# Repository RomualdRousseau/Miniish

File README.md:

# Miniish - Homebrew 6502 Computer

The goal of this project is to build a 8bit game console based on 6502 CPU.
The entire project is strongly inspired by the work and videos of Ben Eater, but
also Javidx9 and his emulator.

## Mother Board

It is basically the same hardware design presented by Ben Eater. I just cleaned
up the adress control logic to have as mush of the 32K RAM available.

The address plan is:

0000 --------------------------------

//   RAM

8000 --------------------------------

//   LO ROM

D000 --------------------------------

//   IRQ Status

D100 --------------------------------

//   PICTURE PROCESSING UNIT (PORT1B)

D200 --------------------------------

//   AUDIO PROCESSING UNIT (PORT2B)

D300 --------------------------------

//   I/O

D400 --------------------------------

//   Reserved

E000 --------------------------------

//   HI ROM

FFFF --------------------------------

## Picture Processing Unit (PPU)

### VGA Card

The card is built using a FPGA and strongly inspired to the NES PPU and the
capability of PICO-8.

The overall specs of the VGA card is 16 colors with a 128x128 display area using
the VGA 640x480 60Hz standard. The 16 colors are the PICO8 palette.

The VGA card is interfaced to the motherboard through a sprite based unit. The
video ram is not mapped to the computer ram but instead, the CPU sends instructions
to a sprite generator very similar to the NES (greatly based on Javidx9
explanations).

The overall spec of the sprite generator is:

* 1 nametables for the background composed of 16 * 16 tiles. Each tile is 8x8
pixels. Scrolling vertical and horizontal modes are supported.

* 256 sprites with tansparency support. Each sprite is also a tile of 8x8 pixels.

* 64 simultaneous sprites on screen and 16 sprites per scanline

* NMI is generated at each vertical blank

## Audio Procesing Unit (APU)

The card is built using a ATMEGA328p at 20Mhz with the library the_synth of Edgar.

The synthetizer has the overall spec: 

* 4 channels at 20KHz

* 4 waveforms: triangle, square, sinus + noise

* 4 envelopes

* modulation

* IRQ0 is generated as the next data frame callback

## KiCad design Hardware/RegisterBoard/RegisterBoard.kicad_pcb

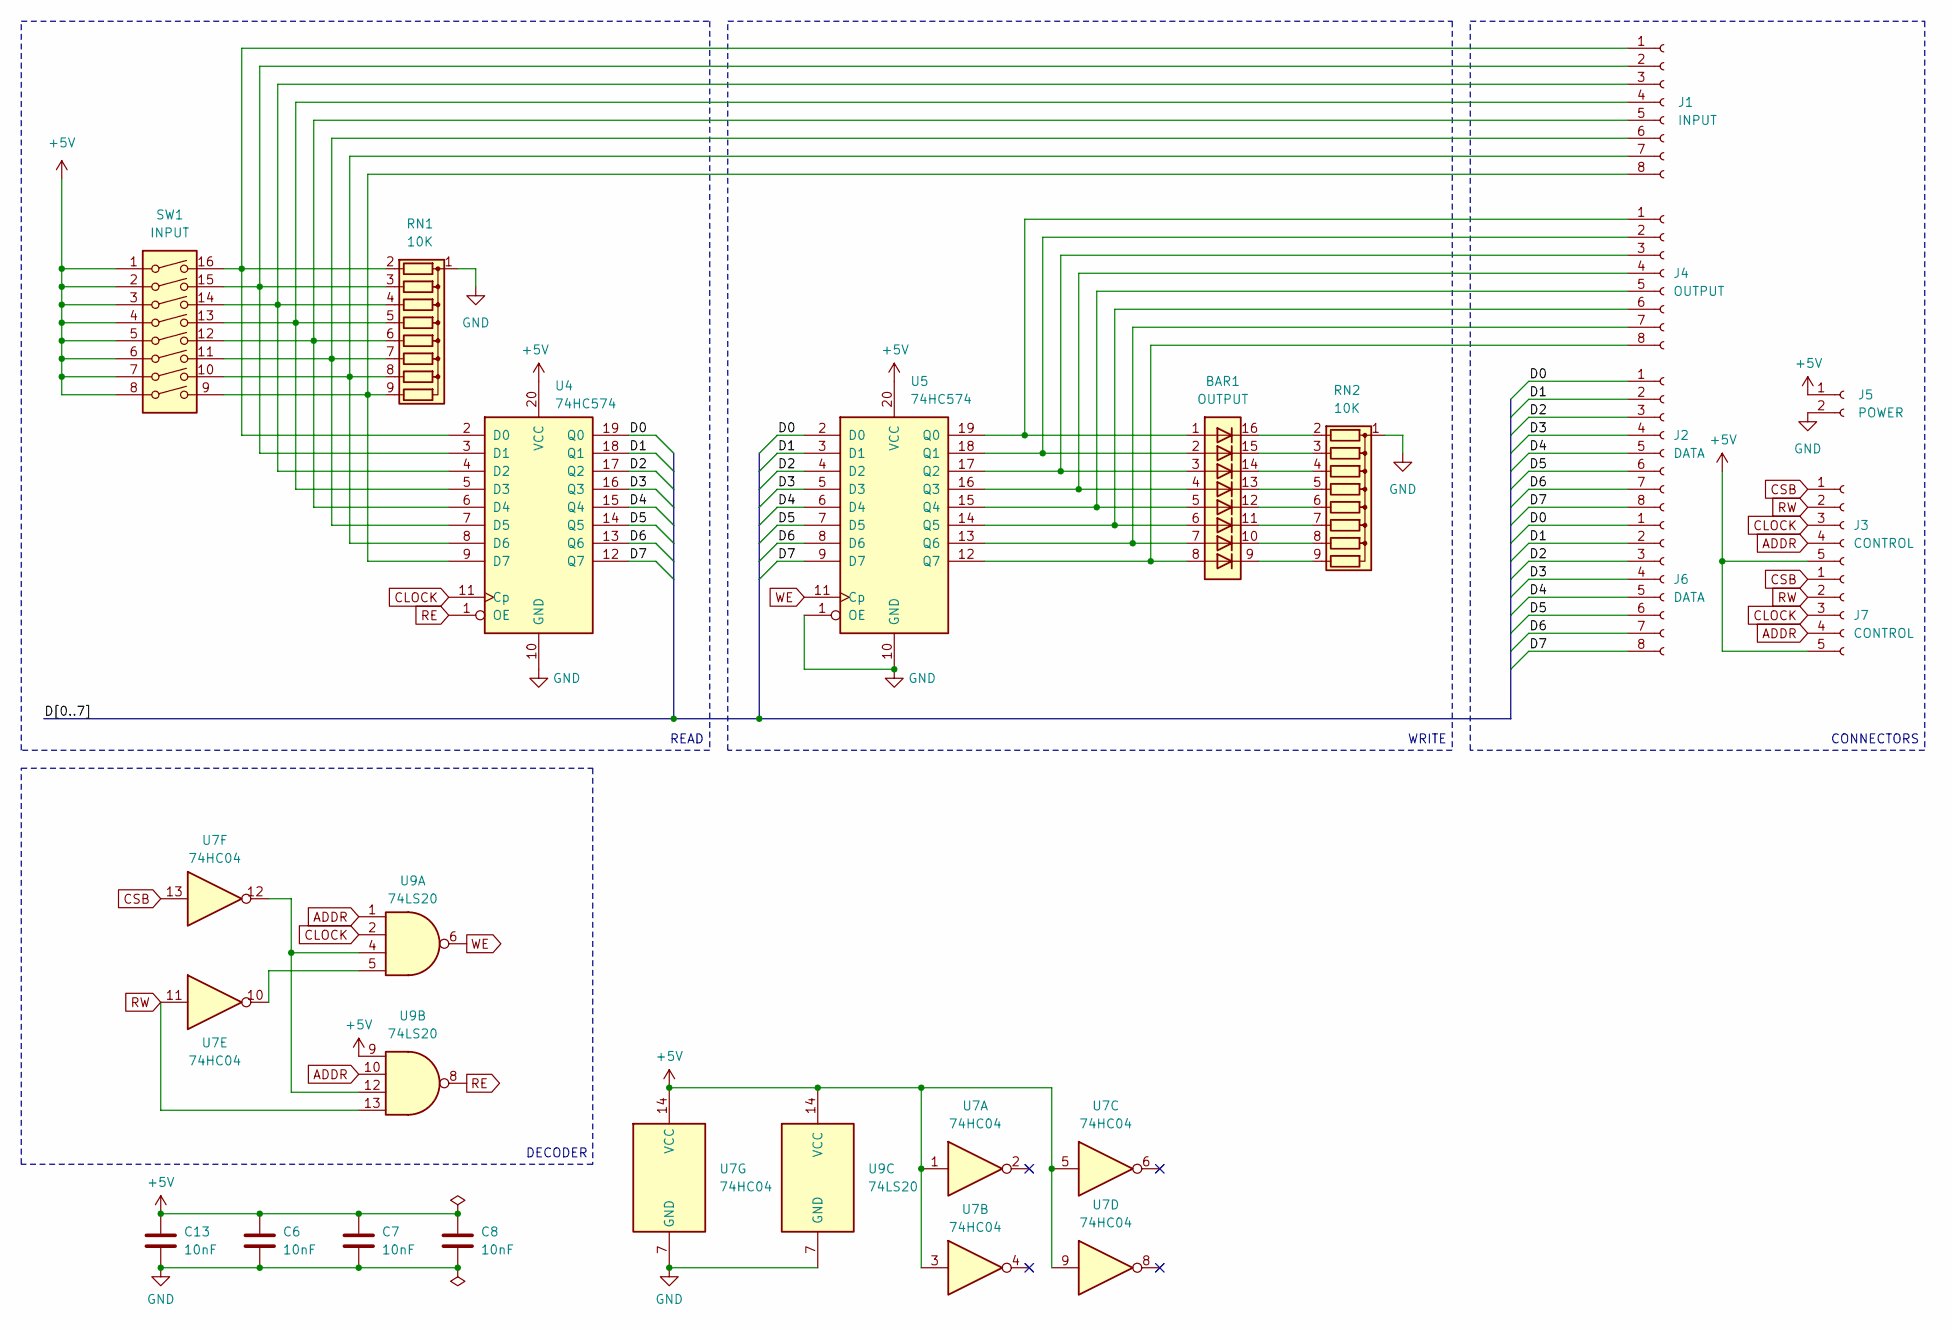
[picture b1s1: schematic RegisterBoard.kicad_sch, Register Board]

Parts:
BAR1: OUTPUT; SSB-LXH100SRW
C6, C7, C8, C13: 10nF; C_Disc_D5.0mm_W2.5mm_P5.00mm
J1: INPUT; PinSocket_1x08_P2.54mm_Vertical
J2, J6: DATA; PinSocket_1x08_P2.54mm_Vertical
J3, J7: CONTROL; PinHeader_1x05_P2.54mm_Vertical
J4: OUTPUT; PinSocket_1x08_P2.54mm_Vertical
J5: POWER; PinSocket_1x02_P2.54mm_Vertical
RN1, RN2: 10K; R_Array_SIP9
SW1: INPUT; SW_DIP_SPSTx08_Slide_9.78x22.5mm_W7.62mm_P2.54mm
U4, U5: 74HC574; DIP-20_W7.62mm
U7: 74HC04; DIP-14_W7.62mm
U9: 74LS20; DIP-14_W7.62mm

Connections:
+5V: C6.1, C7.1, C8.1, C13.1, J3.5, J5.1, J7.5, SW1.1, SW1.2, SW1.3, SW1.4, SW1.5, SW1.6, SW1.7, SW1.8, U4.20 (VCC), U5.20 (VCC), U7.1, U7.3, U7.5, U7.9, U7.14 (VCC), U9.9, U9.14 (VCC)
/D0: J2.1, J6.1, U4.19 (Q0), U5.2 (D0)
/D1: J2.2, J6.2, U4.18 (Q1), U5.3 (D1)
/D2: J2.3, J6.3, U4.17 (Q2), U5.4 (D2)
/D3: J2.4, J6.4, U4.16 (Q3), U5.5 (D3)
/D4: J2.5, J6.5, U4.15 (Q4), U5.6 (D4)
/D5: J2.6, J6.6, U4.14 (Q5), U5.7 (D5)
/D6: J2.7, J6.7, U4.13 (Q6), U5.8 (D6)
/D7: J2.8, J6.8, U4.12 (Q7), U5.9 (D7)
ADDR: J3.4, J7.4, U9.1, U9.10
CLOCK: J3.3, J7.3, U4.11 (Cp), U9.2
CSB: J3.1, J7.1, U7.13
GND: C6.2, C7.2, C8.2, C13.2, J5.2, RN1.1 (common), RN2.1 (common), U4.10 (GND), U5.1 (OE), U5.10 (GND), U7.7 (GND), U9.7 (GND)
unnamed: J1.1, RN1.2 (R1), SW1.16, U4.2 (D0)
unnamed: J1.2, RN1.3 (R2), SW1.15, U4.3 (D1)
unnamed: J1.3, RN1.4 (R3), SW1.14, U4.4 (D2)
unnamed: J1.4, RN1.5 (R4), SW1.13, U4.5 (D3)
unnamed: J1.5, RN1.6 (R5), SW1.12, U4.6 (D4)
unnamed: J1.6, RN1.7 (R6), SW1.11, U4.7 (D5)
unnamed: J1.7, RN1.8 (R7), SW1.10, U4.8 (D6)
unnamed: J1.8, RN1.9 (R8), SW1.9, U4.9 (D7)
unnamed: BAR1.1 (A), J4.1, U5.19 (Q0)
unnamed: BAR1.2 (A), J4.2, U5.18 (Q1)
unnamed: BAR1.3 (A), J4.3, U5.17 (Q2)
unnamed: BAR1.4 (A), J4.4, U5.16 (Q3)
unnamed: BAR1.5 (A), J4.5, U5.15 (Q4)
unnamed: BAR1.6 (A), J4.6, U5.14 (Q5)
unnamed: BAR1.7 (A), J4.7, U5.13 (Q6)
unnamed: BAR1.8 (A), J4.8, U5.12 (Q7)
unnamed: BAR1.16 (K), RN2.2 (R1)
unnamed: BAR1.15 (K), RN2.3 (R2)
unnamed: BAR1.14 (K), RN2.4 (R3)
unnamed: BAR1.13 (K), RN2.5 (R4)
unnamed: BAR1.12 (K), RN2.6 (R5)
unnamed: BAR1.11 (K), RN2.7 (R6)
unnamed: BAR1.10 (K), RN2.8 (R7)
unnamed: BAR1.9 (K), RN2.9 (R8)
unnamed: U7.10, U9.5
unnamed: U7.12, U9.4, U9.12
RE: U4.1 (OE), U9.8
RW: J3.2, J7.2, U7.11, U9.13
WE: U5.11 (Cp), U9.6

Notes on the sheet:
WRITE
CONNECTORS
DECODER
READ

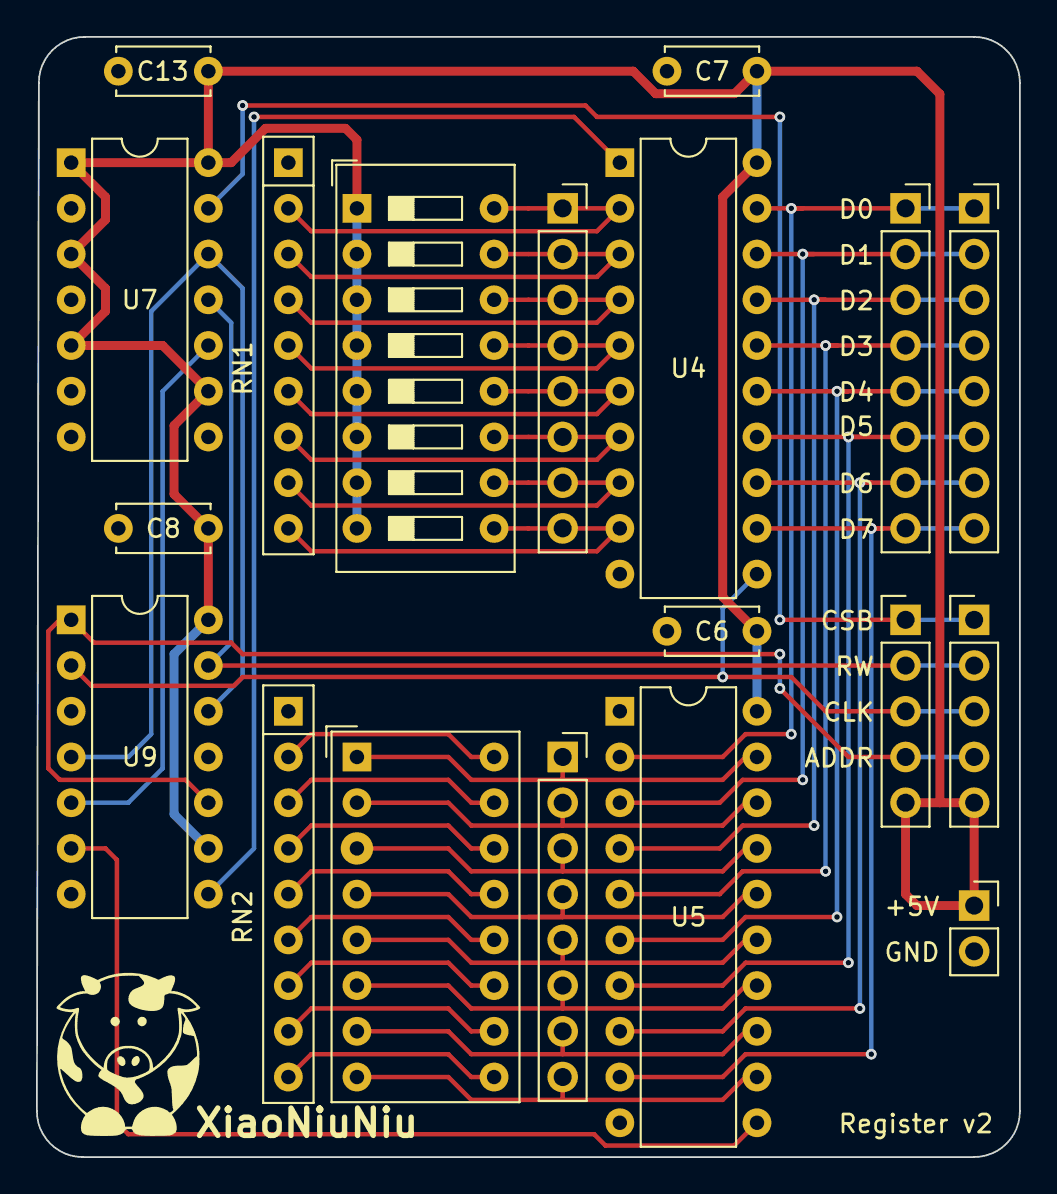
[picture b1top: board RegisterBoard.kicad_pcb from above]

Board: 2 copper layers, 54.6 x 62.2 mm, 20 parts (0 on the bottom side), 42 nets.

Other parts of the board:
XiaoNiuNiu: LOGO; VerySmallCow

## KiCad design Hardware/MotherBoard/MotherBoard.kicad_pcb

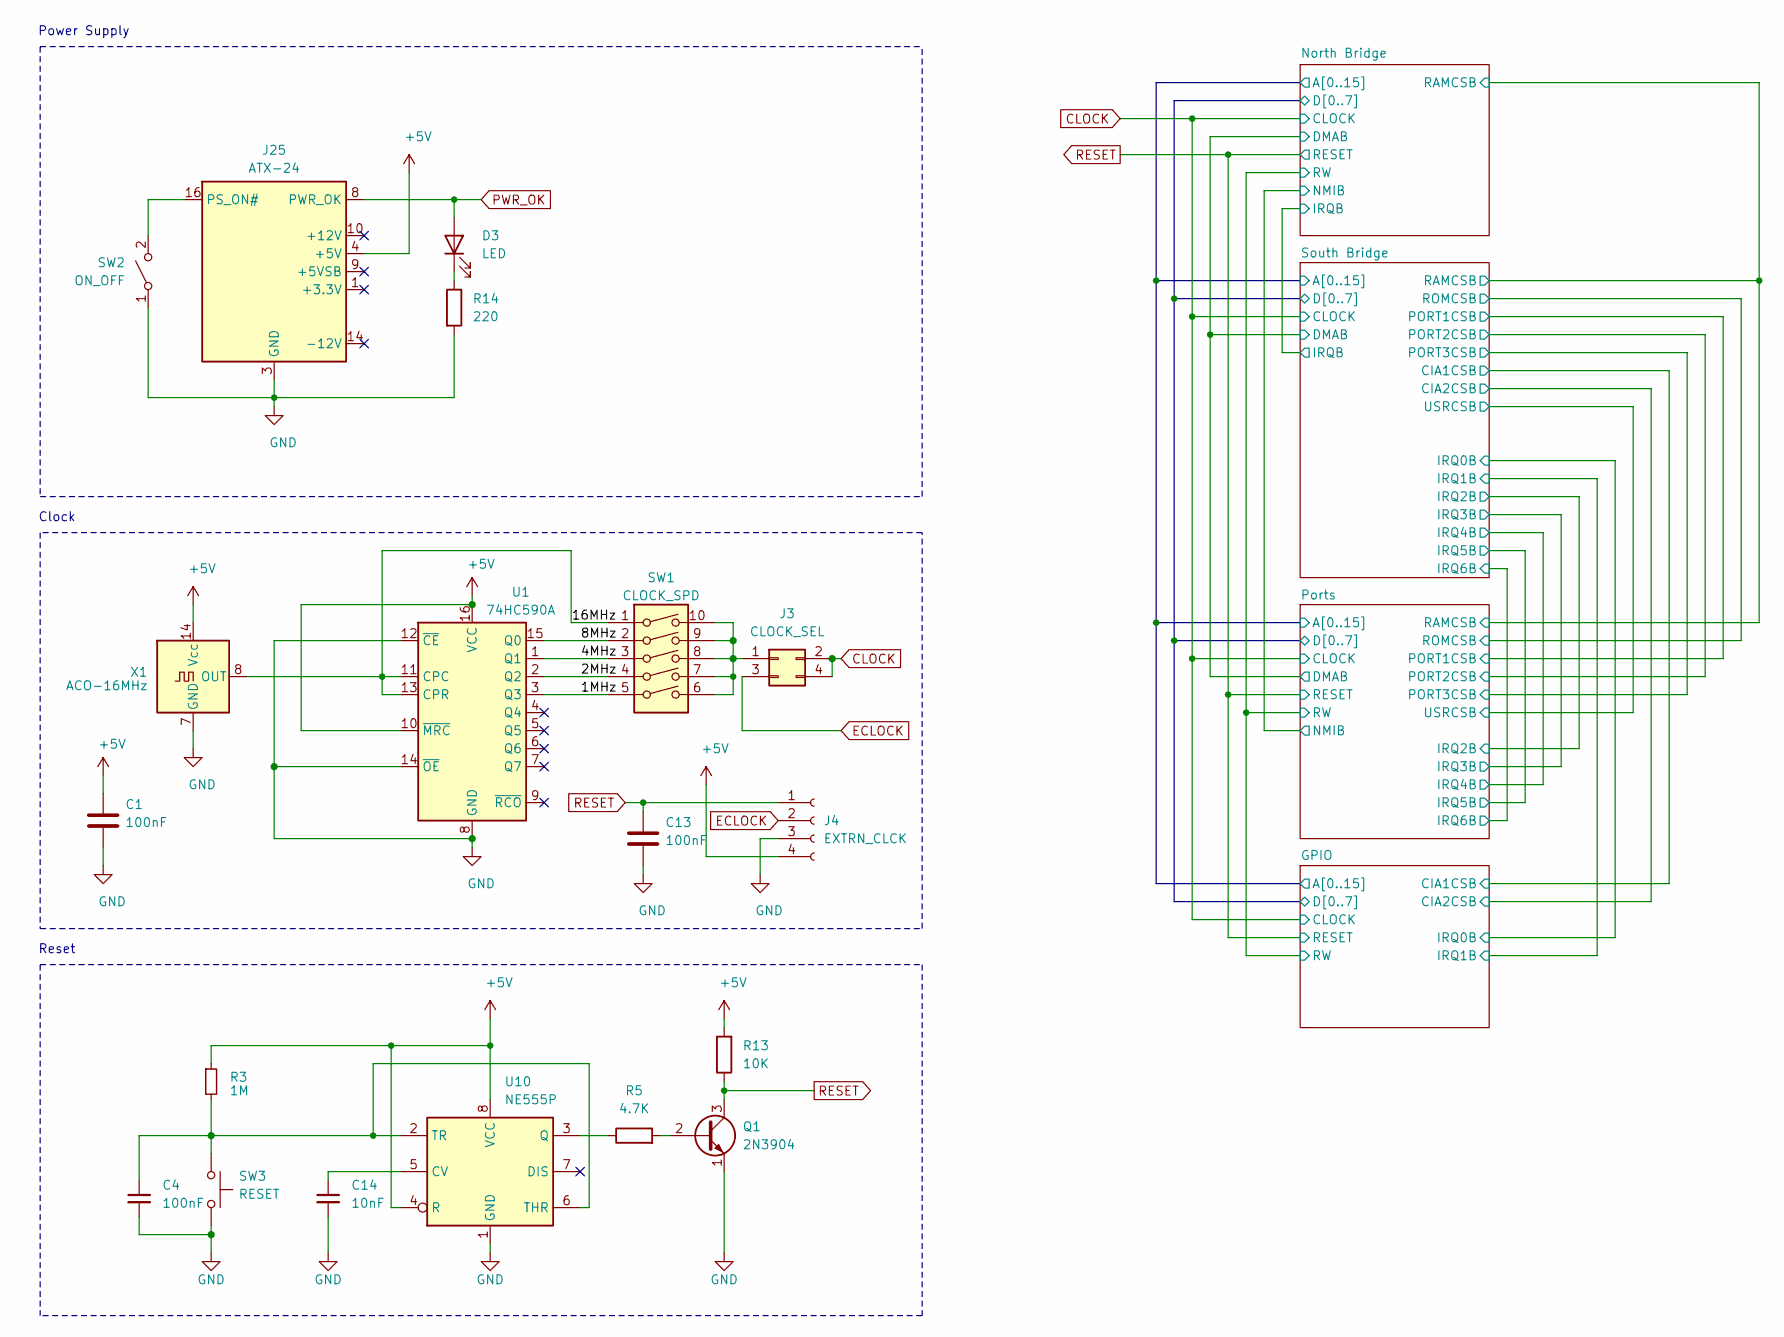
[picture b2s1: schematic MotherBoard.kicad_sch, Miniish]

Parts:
C1, C4, C13: 100nF; C_Disc_D5.0mm_W2.5mm_P2.50mm
C14: 10nF; C_Disc_D5.0mm_W2.5mm_P2.50mm
D3: LED; LED_D5.0mm
J3: CLOCK_SEL; PinHeader_2x02_P2.54mm_Vertical
J4: EXTRN_CLCK; PinHeader_1x04_P2.54mm_Vertical
J25: ATX-24; Molex_Mini-Fit_Jr_5566-24A_2x12_P4.20mm_Vertical
Q1: 2N3904; TO-92_Inline
R3: 1M; R_Axial_DIN0207_L6.3mm_D2.5mm_P10.16mm_Horizontal
R5: 4.7K; R_Axial_DIN0207_L6.3mm_D2.5mm_P10.16mm_Horizontal
R13: 10K; R_Axial_DIN0207_L6.3mm_D2.5mm_P10.16mm_Horizontal
R14: 220; R_Axial_DIN0207_L6.3mm_D2.5mm_P10.16mm_Horizontal
SW1: CLOCK_SPD; SW_DIP_SPSTx05_Slide_6.7x14.26mm_W7.62mm_P2.54mm_LowProfile
SW2: ON_OFF; SW_E-Switch_EG1224_SPDT_Angled
SW3: RESET; SW_Tactile_SPST_Angled_PTS645Vx83-2LFS
U1: 74HC590A; DIP-16_W7.62mm
U10: NE555P; DIP-8_W7.62mm
X1: ACO-16MHz; Oscillator_DIP-14

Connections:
+5V: C1.1, J4.4, J25.4 (+5V), J25.6 (+5V), J25.21 (+5V), J25.22 (+5V), J25.23 (+5V), R3.1, R13.2, U1.10 (~MRC), U1.16 (VCC), U10.4 (R), U10.8 (VCC), X1.14 (Vcc); also elsewhere on the board
/1MHz: SW1.5, U1.3 (Q3)
/2MHz: SW1.4, U1.2 (Q2)
/4MHz: SW1.3, U1.1 (Q1)
/8MHz: SW1.2, U1.15 (Q0)
/16MHz: SW1.1, U1.11 (CPC), U1.13 (CPR), X1.8 (OUT)
CLOCK: J3.2, J3.4; also elsewhere on the board
ECLOCK: J3.3, J4.2
GND: C1.2, C4.2, C13.2, C14.2, J4.3, J25.3 (GND), J25.5 (GND), J25.7 (GND), J25.15 (GND), J25.17 (GND), J25.18 (GND), J25.19 (GND), J25.24 (GND), Q1.1 (E), R14.2, SW2.1 (A), SW3.2, U1.8 (GND), U1.12 (~CE), U1.14 (~OE), U10.1 (GND), X1.7 (GND); also elsewhere on the board
unnamed: D3.1 (K), R14.1
unnamed: J3.1, SW1.6, SW1.7, SW1.8, SW1.9, SW1.10
unnamed: J25.16 (PS_ON#), SW2.2 (B)
unnamed: Q1.2 (B), R5.2
unnamed: C14.1, U10.5 (CV)
unnamed: R5.1, U10.3 (Q)
unnamed: C4.1, R3.2, SW3.1, U10.2 (TR), U10.6 (THR)
PWR_OK: D3.2 (A), J25.8 (PWR_OK)
RESET: C13.1, J4.1, Q1.3 (C), R13.1; also elsewhere on the board

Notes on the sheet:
Reset
Power Supply
Clock

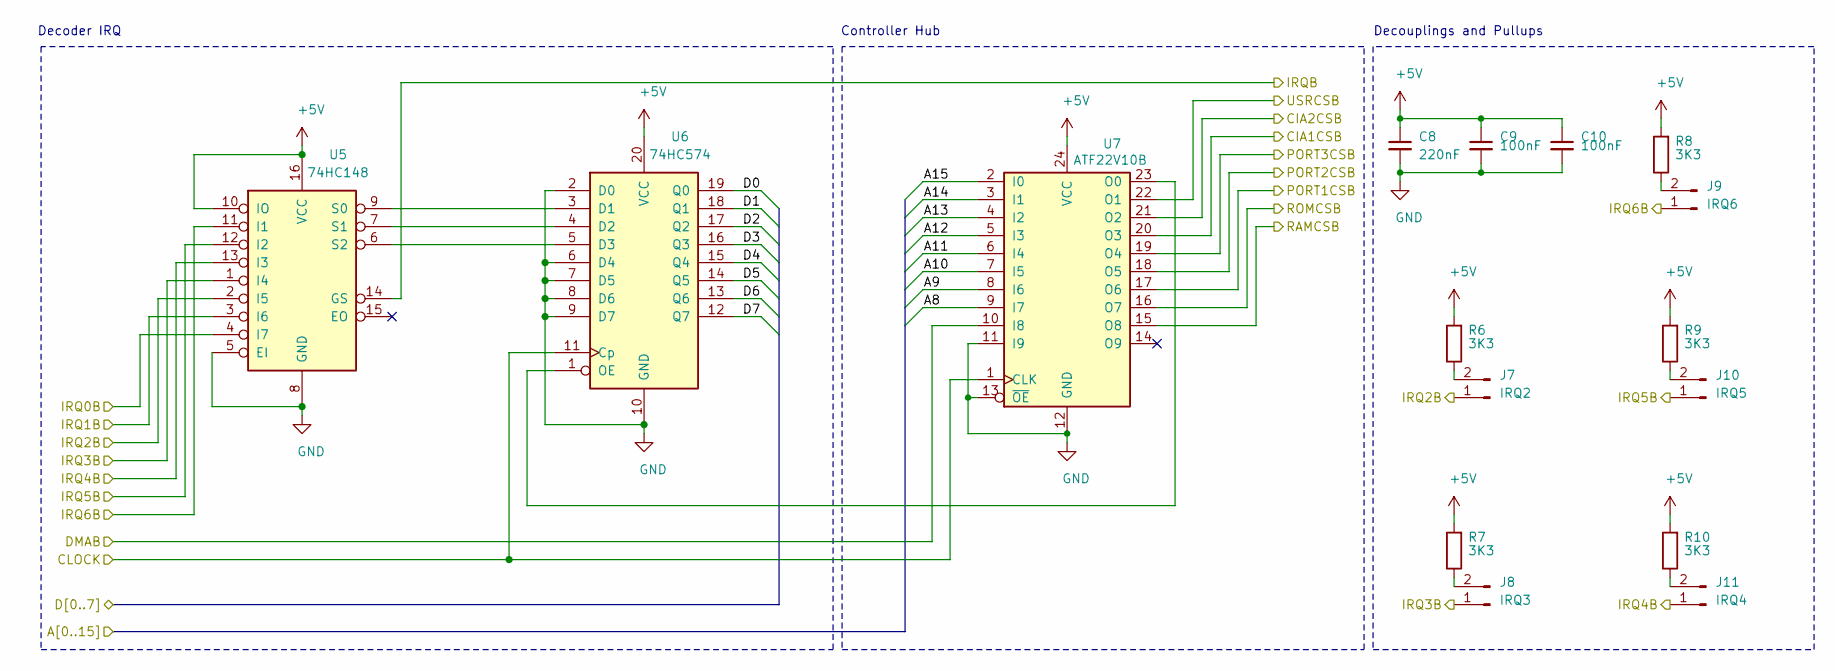
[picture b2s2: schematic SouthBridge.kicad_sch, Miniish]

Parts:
C8: 220nF; C_Disc_D5.0mm_W2.5mm_P2.50mm
C9, C10: 100nF; C_Disc_D5.0mm_W2.5mm_P2.50mm
J7: IRQ2; PinHeader_1x02_P2.54mm_Vertical
J8: IRQ3; PinHeader_1x02_P2.54mm_Vertical
J9: IRQ6; PinHeader_1x02_P2.54mm_Vertical
J10: IRQ5; PinHeader_1x02_P2.54mm_Vertical
J11: IRQ4; PinHeader_1x02_P2.54mm_Vertical
R6, R7, R8, R9, R10: 3K3; R_Axial_DIN0207_L6.3mm_D2.5mm_P10.16mm_Horizontal
U5: 74HC148; DIP-16_W7.62mm
U6: 74HC574; DIP-20_W7.62mm
U7: ATF22V10B; DIP-24_W7.62mm

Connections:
+5V: C8.1, C9.1, C10.1, R6.2, R7.2, R8.2, R9.2, R10.2, U5.10 (IO), U5.16 (VCC), U6.20 (VCC), U7.24 (VCC); also elsewhere on the board
/GPIO/A8: U7.9 (I7); also elsewhere on the board
/GPIO/A9: U7.8 (I6); also elsewhere on the board
/GPIO/A10: U7.7 (I5); also elsewhere on the board
/GPIO/A11: U7.6 (I4); also elsewhere on the board
/GPIO/A12: U7.5 (I3); also elsewhere on the board
/GPIO/A13: U7.4 (I2); also elsewhere on the board
/GPIO/A14: U7.3 (I1); also elsewhere on the board
/GPIO/A15: U7.2 (I0); also elsewhere on the board
/GPIO/CIA1CSB: U7.20 (O3); also elsewhere on the board
/GPIO/CIA2CSB: U7.21 (O2); also elsewhere on the board
/GPIO/D0: U6.19 (Q0); also elsewhere on the board
/GPIO/D1: U6.18 (Q1); also elsewhere on the board
/GPIO/D2: U6.17 (Q2); also elsewhere on the board
/GPIO/D3: U6.16 (Q3); also elsewhere on the board
/GPIO/D4: U6.15 (Q4); also elsewhere on the board
/GPIO/D5: U6.14 (Q5); also elsewhere on the board
/GPIO/D6: U6.13 (Q6); also elsewhere on the board
/GPIO/D7: U6.12 (Q7); also elsewhere on the board
/GPIO/IRQ0B: U5.4 (I7); also elsewhere on the board
/GPIO/IRQ1B: U5.3 (I6); also elsewhere on the board
/North Bridge/DMAB: U7.10 (I8); also elsewhere on the board
/North Bridge/IRQB: U5.14 (GS); also elsewhere on the board
/North Bridge/RAMCSB: U7.15 (O8); also elsewhere on the board
/Ports/IRQ2B: J7.1, U5.2 (I5)
/Ports/IRQ3B: J8.1, U5.1 (I4); also elsewhere on the board
/Ports/IRQ4B: J11.1, U5.13 (I3); also elsewhere on the board
/Ports/IRQ5B: J10.1, U5.12 (I2); also elsewhere on the board
/Ports/IRQ6B: J9.1, U5.11 (I1); also elsewhere on the board
/Ports/PORT1CSB: U7.17 (O6); also elsewhere on the board
/Ports/PORT2CSB: U7.18 (O5); also elsewhere on the board
/Ports/PORT3CSB: U7.19 (O4); also elsewhere on the board
/Ports/ROMCSB: U7.16 (O7); also elsewhere on the board
/Ports/USRCSB: U7.22 (O1)
CLOCK: U6.11 (Cp), U7.1 (CLK); also elsewhere on the board
GND: C8.2, C9.2, C10.2, U5.5 (EI), U5.8 (GND), U6.2 (D0), U6.6 (D4), U6.7 (D5), U6.8 (D6), U6.9 (D7), U6.10 (GND), U7.11 (I9), U7.12 (GND), U7.13 (~OE); also elsewhere on the board
unnamed: J7.2, R6.1
unnamed: J8.2, R7.1
unnamed: J9.2, R8.1
unnamed: J10.2, R9.1
unnamed: J11.2, R10.1
unnamed: U5.9 (S0), U6.3 (D1)
unnamed: U5.7 (S1), U6.4 (D2)
unnamed: U5.6 (S2), U6.5 (D3)
unnamed: U6.1 (OE), U7.23 (O0)

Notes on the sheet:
Decouplings and Pullups
Decoder IRQ
Controller Hub

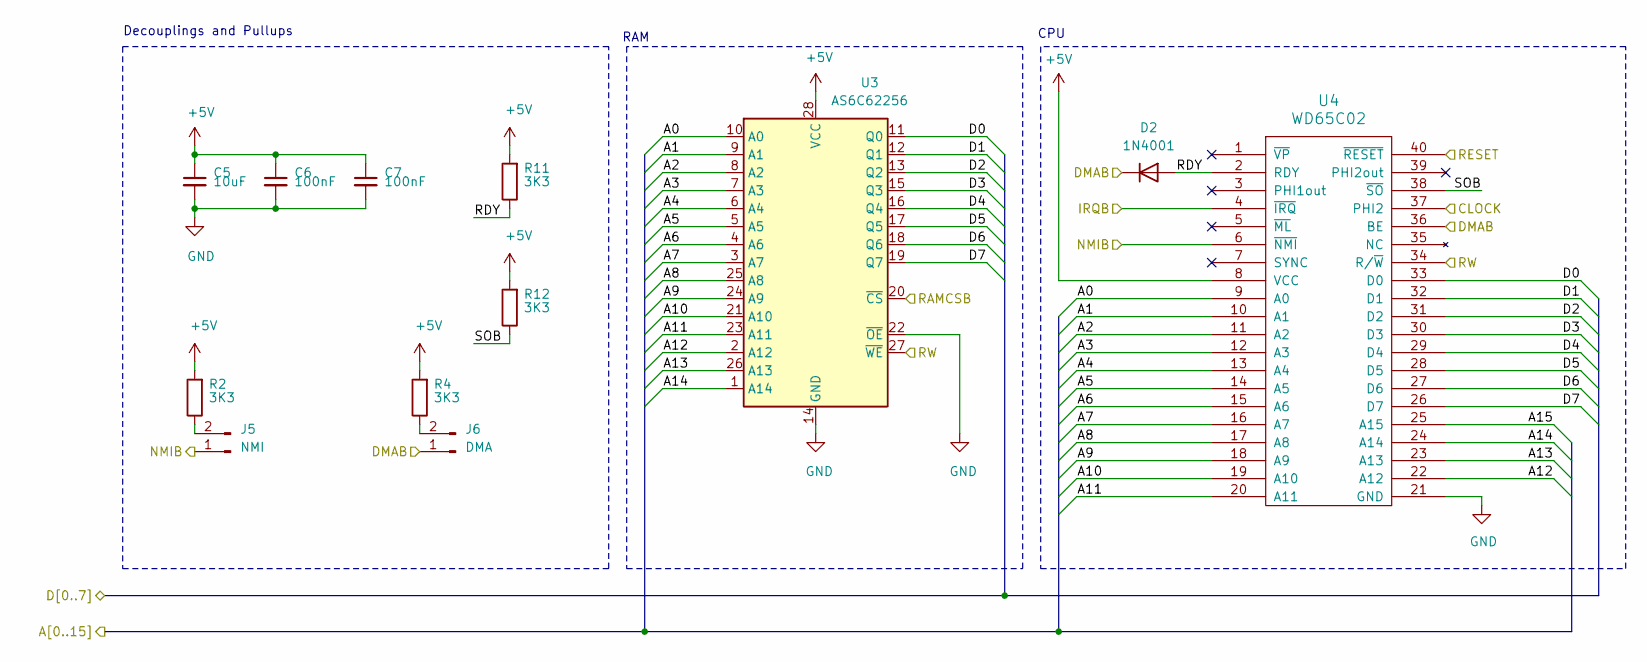
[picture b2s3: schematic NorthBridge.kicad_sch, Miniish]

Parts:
C5: 10uF; C_Radial_D5.0mm_H11.0mm_P2.00mm
C6, C7: 100nF; C_Disc_D5.0mm_W2.5mm_P2.50mm
D2: 1N4001; D_DO-41_SOD81_P10.16mm_Horizontal
J5: NMI; PinHeader_1x02_P2.54mm_Vertical
J6: DMA; PinHeader_1x02_P2.54mm_Vertical
R2, R4, R11, R12: 3K3; R_Axial_DIN0207_L6.3mm_D2.5mm_P10.16mm_Horizontal
U3: AS6C62256; DIP-28_W15.24mm
U4: WD65C02; DIP-40_W15.24mm

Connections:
+5V: C5.1, C6.1, C7.1, R2.2, R4.2, R11.2, R12.2, U3.28 (VCC), U4.8 (VCC); also elsewhere on the board
/GPIO/A0: U3.10 (A0), U4.9 (A0); also elsewhere on the board
/GPIO/A1: U3.9 (A1), U4.10 (A1); also elsewhere on the board
/GPIO/A2: U3.8 (A2), U4.11 (A2); also elsewhere on the board
/GPIO/A3: U3.7 (A3), U4.12 (A3); also elsewhere on the board
/GPIO/A4: U3.6 (A4), U4.13 (A4); also elsewhere on the board
/GPIO/A5: U3.5 (A5), U4.14 (A5); also elsewhere on the board
/GPIO/A6: U3.4 (A6), U4.15 (A6); also elsewhere on the board
/GPIO/A7: U3.3 (A7), U4.16 (A7); also elsewhere on the board
/GPIO/A8: U3.25 (A8), U4.17 (A8); also elsewhere on the board
/GPIO/A9: U3.24 (A9), U4.18 (A9); also elsewhere on the board
/GPIO/A10: U3.21 (A10), U4.19 (A10); also elsewhere on the board
/GPIO/A11: U3.23 (A11), U4.20 (A11); also elsewhere on the board
/GPIO/A12: U3.2 (A12), U4.22 (A12); also elsewhere on the board
/GPIO/A13: U3.26 (A13), U4.23 (A13); also elsewhere on the board
/GPIO/A14: U3.1 (A14), U4.24 (A14); also elsewhere on the board
/GPIO/A15: U4.25 (A15); also elsewhere on the board
/GPIO/D0: U3.11 (Q0), U4.33 (D0); also elsewhere on the board
/GPIO/D1: U3.12 (Q1), U4.32 (D1); also elsewhere on the board
/GPIO/D2: U3.13 (Q2), U4.31 (D2); also elsewhere on the board
/GPIO/D3: U3.15 (Q3), U4.30 (D3); also elsewhere on the board
/GPIO/D4: U3.16 (Q4), U4.29 (D4); also elsewhere on the board
/GPIO/D5: U3.17 (Q5), U4.28 (D5); also elsewhere on the board
/GPIO/D6: U3.18 (Q6), U4.27 (D6); also elsewhere on the board
/GPIO/D7: U3.19 (Q7), U4.26 (D7); also elsewhere on the board
/GPIO/RW: U3.27 (~WE), U4.34 (R/~W); also elsewhere on the board
/North Bridge/DMAB: D2.1 (K), J6.1, U4.36 (BE); also elsewhere on the board
/North Bridge/IRQB: U4.4 (~IRQ); also elsewhere on the board
/North Bridge/NMIB: J5.1, U4.6 (~NMI); also elsewhere on the board
/North Bridge/RAMCSB: U3.20 (~CS); also elsewhere on the board
/North Bridge/RDY: D2.2 (A), R11.1, U4.2 (RDY)
/North Bridge/SOB: R12.1, U4.38 (~SO)
CLOCK: U4.37 (PHI2); also elsewhere on the board
GND: C5.2, C6.2, C7.2, U3.14 (GND), U3.22 (~OE), U4.21 (GND); also elsewhere on the board
unnamed: J5.2, R2.1
unnamed: J6.2, R4.1
RESET: U4.40 (~RESET); also elsewhere on the board

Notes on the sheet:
CPU
RAM
Decouplings and Pullups

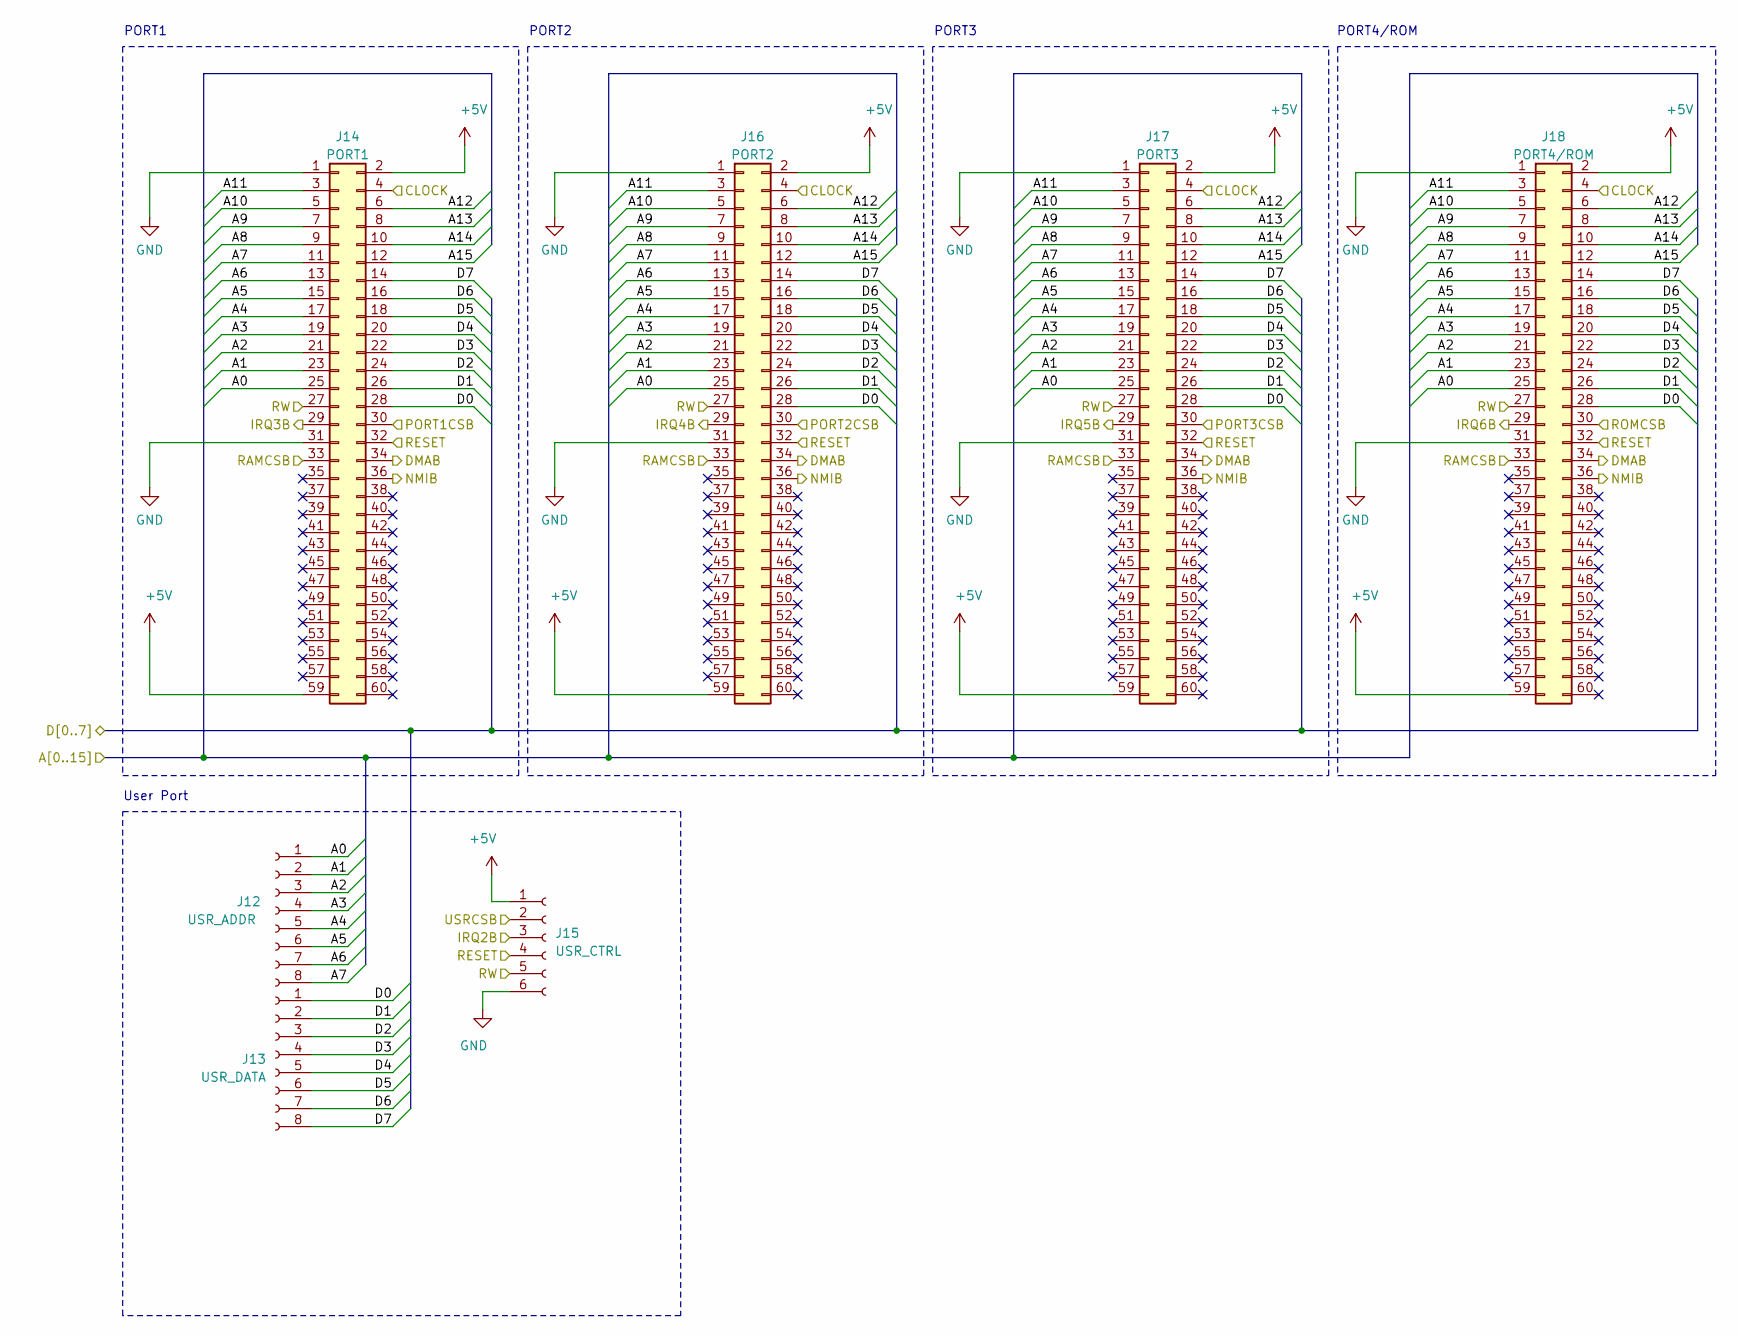
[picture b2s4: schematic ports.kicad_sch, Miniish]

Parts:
J12: USR_ADDR; PinHeader_1x08_P2.54mm_Vertical
J13: USR_DATA; PinHeader_1x08_P2.54mm_Vertical
J14: PORT1; NES_Cartdrige
J15: USR_CTRL; PinHeader_2x03_P2.54mm_Vertical
J16: PORT2; NES_Cartdrige
J17: PORT3; NES_Cartdrige
J18: PORT4/ROM; NES_Cartdrige

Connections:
+5V: J14.2, J14.59, J15.1, J16.2, J16.59, J17.2, J17.59, J18.2, J18.59; also elsewhere on the board
/GPIO/A0: J12.1, J14.25, J16.25, J17.25, J18.25; also elsewhere on the board
/GPIO/A1: J12.2, J14.23, J16.23, J17.23, J18.23; also elsewhere on the board
/GPIO/A2: J12.3, J14.21, J16.21, J17.21, J18.21; also elsewhere on the board
/GPIO/A3: J12.4, J14.19, J16.19, J17.19, J18.19; also elsewhere on the board
/GPIO/A4: J12.5, J14.17, J16.17, J17.17, J18.17; also elsewhere on the board
/GPIO/A5: J12.6, J14.15, J16.15, J17.15, J18.15; also elsewhere on the board
/GPIO/A6: J12.7, J14.13, J16.13, J17.13, J18.13; also elsewhere on the board
/GPIO/A7: J12.8, J14.11, J16.11, J17.11, J18.11; also elsewhere on the board
/GPIO/A8: J14.9, J16.9, J17.9, J18.9; also elsewhere on the board
/GPIO/A9: J14.7, J16.7, J17.7, J18.7; also elsewhere on the board
/GPIO/A10: J14.5, J16.5, J17.5, J18.5; also elsewhere on the board
/GPIO/A11: J14.3, J16.3, J17.3, J18.3; also elsewhere on the board
/GPIO/A12: J14.6, J16.6, J17.6, J18.6; also elsewhere on the board
/GPIO/A13: J14.8, J16.8, J17.8, J18.8; also elsewhere on the board
/GPIO/A14: J14.10, J16.10, J17.10, J18.10; also elsewhere on the board
/GPIO/A15: J14.12, J16.12, J17.12, J18.12; also elsewhere on the board
/GPIO/D0: J13.1, J14.28, J16.28, J17.28, J18.28; also elsewhere on the board
/GPIO/D1: J13.2, J14.26, J16.26, J17.26, J18.26; also elsewhere on the board
/GPIO/D2: J13.3, J14.24, J16.24, J17.24, J18.24; also elsewhere on the board
/GPIO/D3: J13.4, J14.22, J16.22, J17.22, J18.22; also elsewhere on the board
/GPIO/D4: J13.5, J14.20, J16.20, J17.20, J18.20; also elsewhere on the board
/GPIO/D5: J13.6, J14.18, J16.18, J17.18, J18.18; also elsewhere on the board
/GPIO/D6: J13.7, J14.16, J16.16, J17.16, J18.16; also elsewhere on the board
/GPIO/D7: J13.8, J14.14, J16.14, J17.14, J18.14; also elsewhere on the board
/GPIO/RW: J14.27, J15.5, J16.27, J17.27, J18.27; also elsewhere on the board
/North Bridge/DMAB: J14.34, J16.34, J17.34, J18.34; also elsewhere on the board
/North Bridge/NMIB: J14.36, J16.36, J17.36, J18.36; also elsewhere on the board
/North Bridge/RAMCSB: J14.33, J16.33, J17.33, J18.33; also elsewhere on the board
/Ports/IRQ3B: J14.29; also elsewhere on the board
/Ports/IRQ4B: J16.29; also elsewhere on the board
/Ports/IRQ5B: J17.29; also elsewhere on the board
/Ports/IRQ6B: J18.29; also elsewhere on the board
/Ports/PORT1CSB: J14.30; also elsewhere on the board
/Ports/PORT2CSB: J16.30; also elsewhere on the board
/Ports/PORT3CSB: J17.30; also elsewhere on the board
/Ports/ROMCSB: J18.30; also elsewhere on the board
CLOCK: J14.4, J16.4, J17.4, J18.4; also elsewhere on the board
GND: J14.1, J14.31, J15.6, J16.1, J16.31, J17.1, J17.31, J18.1, J18.31; also elsewhere on the board
RESET: J14.32, J15.4, J16.32, J17.32, J18.32; also elsewhere on the board

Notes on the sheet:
PORT1
PORT3
PORT4/ROM
User Port
PORT2

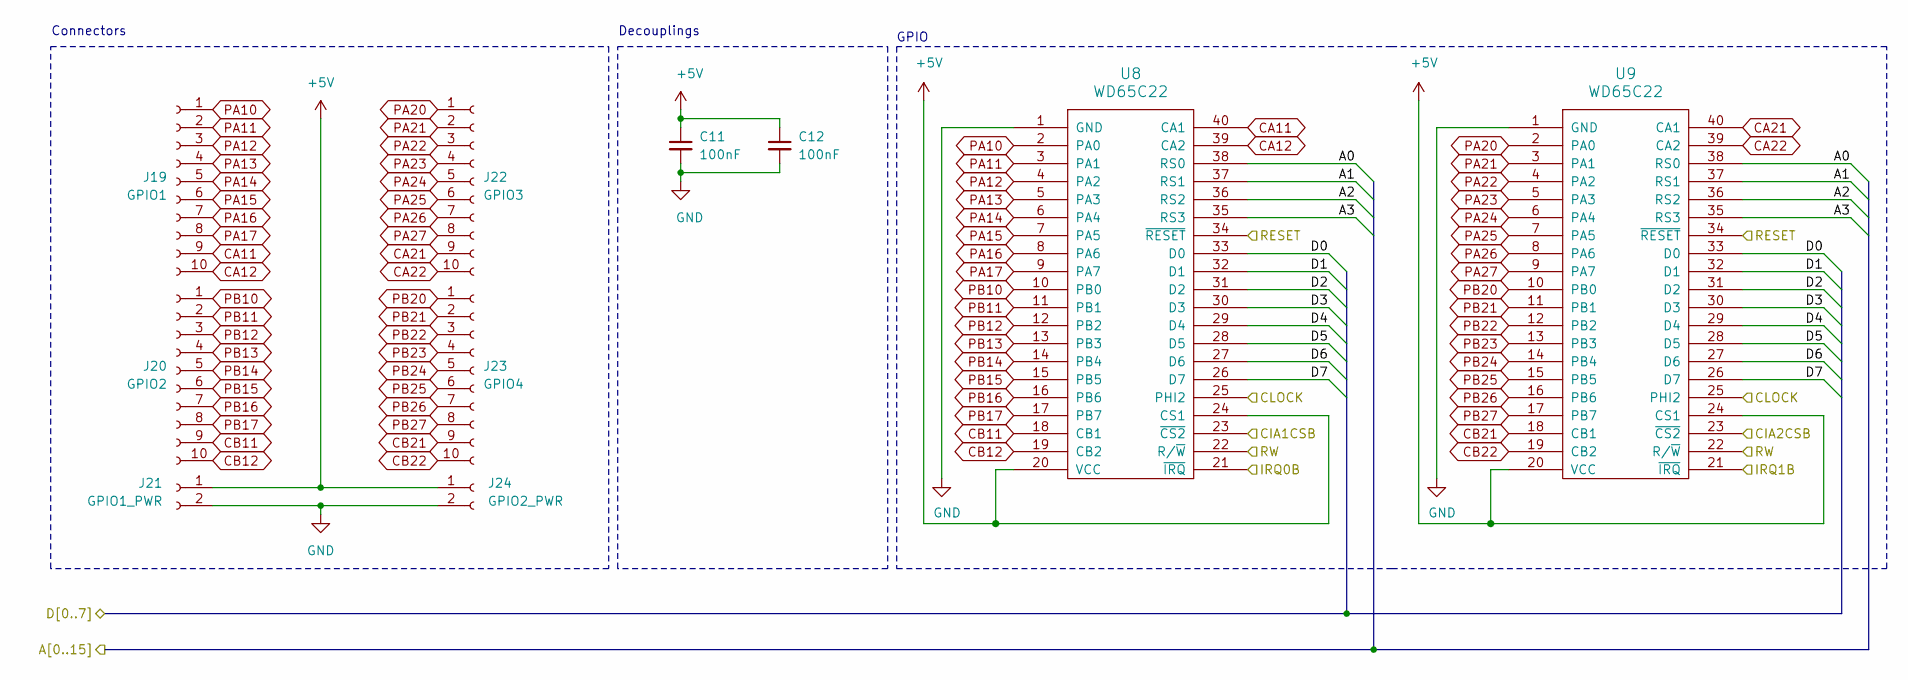
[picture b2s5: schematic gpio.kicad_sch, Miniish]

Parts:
C11, C12: 100nF; C_Disc_D5.0mm_W2.5mm_P2.50mm
J19: GPIO1; PinSocket_1x10_P2.54mm_Vertical
J20: GPIO2; PinSocket_1x10_P2.54mm_Vertical
J21: GPIO1_PWR; PinSocket_1x02_P2.54mm_Vertical
J22: GPIO3; PinSocket_1x10_P2.54mm_Vertical
J23: GPIO4; PinSocket_1x10_P2.54mm_Vertical
J24: GPIO2_PWR; PinSocket_1x02_P2.54mm_Vertical
U8, U9: WD65C22; DIP-40_W15.24mm

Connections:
+5V: C11.1, C12.1, J21.1, J24.1, U8.20 (VCC), U8.24 (CS1), U9.20 (VCC), U9.24 (CS1); also elsewhere on the board
/GPIO/A0: U8.38 (RS0), U9.38 (RS0); also elsewhere on the board
/GPIO/A1: U8.37 (RS1), U9.37 (RS1); also elsewhere on the board
/GPIO/A2: U8.36 (RS2), U9.36 (RS2); also elsewhere on the board
/GPIO/A3: U8.35 (RS3), U9.35 (RS3); also elsewhere on the board
/GPIO/CIA1CSB: U8.23 (~CS2); also elsewhere on the board
/GPIO/CIA2CSB: U9.23 (~CS2); also elsewhere on the board
/GPIO/D0: U8.33 (D0), U9.33 (D0); also elsewhere on the board
/GPIO/D1: U8.32 (D1), U9.32 (D1); also elsewhere on the board
/GPIO/D2: U8.31 (D2), U9.31 (D2); also elsewhere on the board
/GPIO/D3: U8.30 (D3), U9.30 (D3); also elsewhere on the board
/GPIO/D4: U8.29 (D4), U9.29 (D4); also elsewhere on the board
/GPIO/D5: U8.28 (D5), U9.28 (D5); also elsewhere on the board
/GPIO/D6: U8.27 (D6), U9.27 (D6); also elsewhere on the board
/GPIO/D7: U8.26 (D7), U9.26 (D7); also elsewhere on the board
/GPIO/IRQ0B: U8.21 (~IRQ); also elsewhere on the board
/GPIO/IRQ1B: U9.21 (~IRQ); also elsewhere on the board
/GPIO/RW: U8.22 (R/~W), U9.22 (R/~W); also elsewhere on the board
CA11: J19.9, U8.40 (CA1)
CA12: J19.10, U8.39 (CA2)
CA21: J22.9, U9.40 (CA1)
CA22: J22.10, U9.39 (CA2)
CB11: J20.9, U8.18 (CB1)
CB12: J20.10, U8.19 (CB2)
CB21: J23.9, U9.18 (CB1)
CB22: J23.10, U9.19 (CB2)
CLOCK: U8.25 (PHI2), U9.25 (PHI2); also elsewhere on the board
GND: C11.2, C12.2, J21.2, J24.2, U8.1 (GND), U9.1 (GND); also elsewhere on the board
PA10: J19.1, U8.2 (PA0)
PA11: J19.2, U8.3 (PA1)
PA12: J19.3, U8.4 (PA2)
PA13: J19.4, U8.5 (PA3)
PA14: J19.5, U8.6 (PA4)
PA15: J19.6, U8.7 (PA5)
PA16: J19.7, U8.8 (PA6)
PA17: J19.8, U8.9 (PA7)
PA20: J22.1, U9.2 (PA0)
PA21: J22.2, U9.3 (PA1)
PA22: J22.3, U9.4 (PA2)
PA23: J22.4, U9.5 (PA3)
PA24: J22.5, U9.6 (PA4)
PA25: J22.6, U9.7 (PA5)
PA26: J22.7, U9.8 (PA6)
PA27: J22.8, U9.9 (PA7)
PB10: J20.1, U8.10 (PB0)
PB11: J20.2, U8.11 (PB1)
PB12: J20.3, U8.12 (PB2)
PB13: J20.4, U8.13 (PB3)
PB14: J20.5, U8.14 (PB4)
PB15: J20.6, U8.15 (PB5)
PB16: J20.7, U8.16 (PB6)
PB17: J20.8, U8.17 (PB7)
PB20: J23.1, U9.10 (PB0)
PB21: J23.2, U9.11 (PB1)
PB22: J23.3, U9.12 (PB2)
PB23: J23.4, U9.13 (PB3)
PB24: J23.5, U9.14 (PB4)
PB25: J23.6, U9.15 (PB5)
PB26: J23.7, U9.16 (PB6)
PB27: J23.8, U9.17 (PB7)
RESET: U8.34 (~RESET), U9.34 (~RESET); also elsewhere on the board

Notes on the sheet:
Connectors
GPIO
Decouplings
